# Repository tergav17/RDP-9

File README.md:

# RDP-9

## Project Description

This project aims to build an ISA-compatible clone of the DEC PDP-9 system using primarily technology from the late 1970s - early 1980s period. I did this to ensure my design followed the same constraints that later genuine minicomputer systems were built with, while being able to significantly reduce the size and complexity compared to an actual PDP-9. The specifics are as follows

- Use only 74-series logic and other similar TTL logic level parts that would be available around the later 1970s timeframe. The exception to this is RAM, which I plan to use more “modern” SRAM chips instead of torturing myself with dynamic RAM.
- No FPGAs, PALs, GALs, microcontrollers, etc in the main processor path. The only exception to this is using standard 27C style ROM chips to hold the microcode.
- Usage of a period correct microcontroller or microprocessor for the disk / drum subsystem. Using another simpler processor to control complex devices like disks was done frequently on other minicomputer designs, so I’ll be doing it here too.

My end goal is to build a system that is capable of running most of the interesting software of the period. This includes DECsys, ADSS, DOS-15, and UNIX V0. To do this, the system will need:

- Full compatibility with the PDP-9 instruction set. This includes EAE instructions and extended memory
- The ability to hook up to a real or emulated paper tape punch / reader.
- The ability to hook up to a real or emulated ASR-33 teletype or similar serial terminal
- 8" floppy drive interface in place of DECtape. Software will require patching but it's better than trying to emulate DECtape
- IDE hard drive support using RB09/RF09 interface 

## Theory of Operation

Due to the complexity involved with the architecture of the DEC PDP-9, the system is split into two subsystems:

The first subsystem is the processor itself. It has a full 18-bit datapath with 15-bit address bus, and is implemented entirely using TTL logic.

The second subsystem is the I/O bus. This is directly controlled by the processor itself and is capable of servicing the following operations:

- Device interrupts
- IOT transactions
- Add-to-memory operations
- Data channel transfers
- DMA transfers
- READ-IN operation

### Device Interrupts

Device interrupts simply tell the processor to begin an interrupt operation. When an interrupt is accepted, the I/O bus will be notified of the action
and is responsible for turning off the "Program Interrupt" flag. If this does not happen, interrupts will continuously loop. 

#### Steps:

1. Interrupt is accepted. MA is completely zeroed and the "INTERRUPT_DETECT" pulse is asserted for this clock cycle.

2. PC is stored in MB, OB

3. The logical OR of MB and OB is place in CORE at MA. The crossbar will add the LINK and MEMM flags

4. MA + 1 is placed in the PC. Extend is enabled to ensure that bank 0 is selected. The next fetch will ignore device requests

### IOT Transactions

IOT transactions allow data to be transferred to or from the accumulator. IOTs also allow for skips to be requested. Every IOT is treated by the CPU
as a Read-Modify-Write operation. By using the "EXTRN" signal, devices can notify the processor to read from the I/O bus instead of the writeback register.
When the I/O bus is being sampled, the "IOT_SKIP" signal can be asserted to tell the processor to perform an addition increment of the program counter.

A wait signal is sampled at the beginning of the IOT as well. This can be used to add cycles to the writeback phase of the IOT if the device needs it.

#### Steps:

1. IOT transaction begins. Device address is placed on the I/O address bus. AC (or 0 if the flag is set) is written to the WRTBK register.

2. Signal "IOT_PULSE" is asserted.

3. Signal "IOT_PULSE" remains asserted. External input is sampled into MB. Signal "EXTRN" must be asserted to take value from device bus.

4. IF "IOT_WAIT" is asserted, goto step 3 in place. No IOT signals are asserted. Interally, the CPU is performing the logical OR and writeback of potential provided data.

5. No IOT signals are asserted. Internally, the CPU will perform the skip here if it has been requested. The next fetch cycle will ignore interrupts and device requests.

### Device Requests

The final three transaction types (Add-to-memory, data-channels, and DMA transfers all share the "device request" pathway.

#### Steps:

1. Signal "REQ_ADDR_PHASE" and "DEV_REQ_GRANT" asserted and held. External value written to MA.

2. If DMA is selected, core is read at MA and written to WRTBK with next as step 8. Otherwise core is read at MA and written to MB, OB. "REQ_ADDR_PHASE" held

3. Value in MB, OB incremented and written back to core at MA and OB. "REQ_ADDR_PHASE" held

4. Value in MA incremented. If add to memory selected, Jump to fetch without device request logic. "INCREMENT_ZERO_PUSLE" will be generated if needed. "REQ_ADDR_PHASE" held

5. Core is read at MA and written to MB, OB.

6. Value in MB, OB incremented and written back to core at MA and MA

7. Core is read at MA and written to WRTBK

8. External value written to core at MA. "DEV_REQ_GRANT" reset. Jump to fetch without device request logic

### READ-IN Operation

The read-in is used to transfer a set series of words into memory from one of the I/O devices. Only one I/O device can be be allowed to respond to READ-IN
at any one time. When a READ-IN transaction is active, the CPU will stall until the designated device signals that it is ready. The device will either signal
the CPU to commence another READ-IN cycle, or to terminate the READ-IN after any given transfer.

#### Steps:

1. SWR is moved into PC

2. "READ_IN_PULSE" is asserted, step will loop till either "IOT_WAIT" or "IOT_SKIP" are asserted.

3. "READ_IN_PULSE" remains asserted. EXTRN is moved into core at PC. Continue having the constant value asserted.

4. "READ_IN_PULSE" reset. If "IOT_SKIP" is asserted, jump to CONT logic. Otherwise move PC + 1 into PC

5. Null phase, "READ_IN_PULSE" remains reset.

6. Null phase, "READ_IN_PULSE" remains reset. Jump to step 2 on completion

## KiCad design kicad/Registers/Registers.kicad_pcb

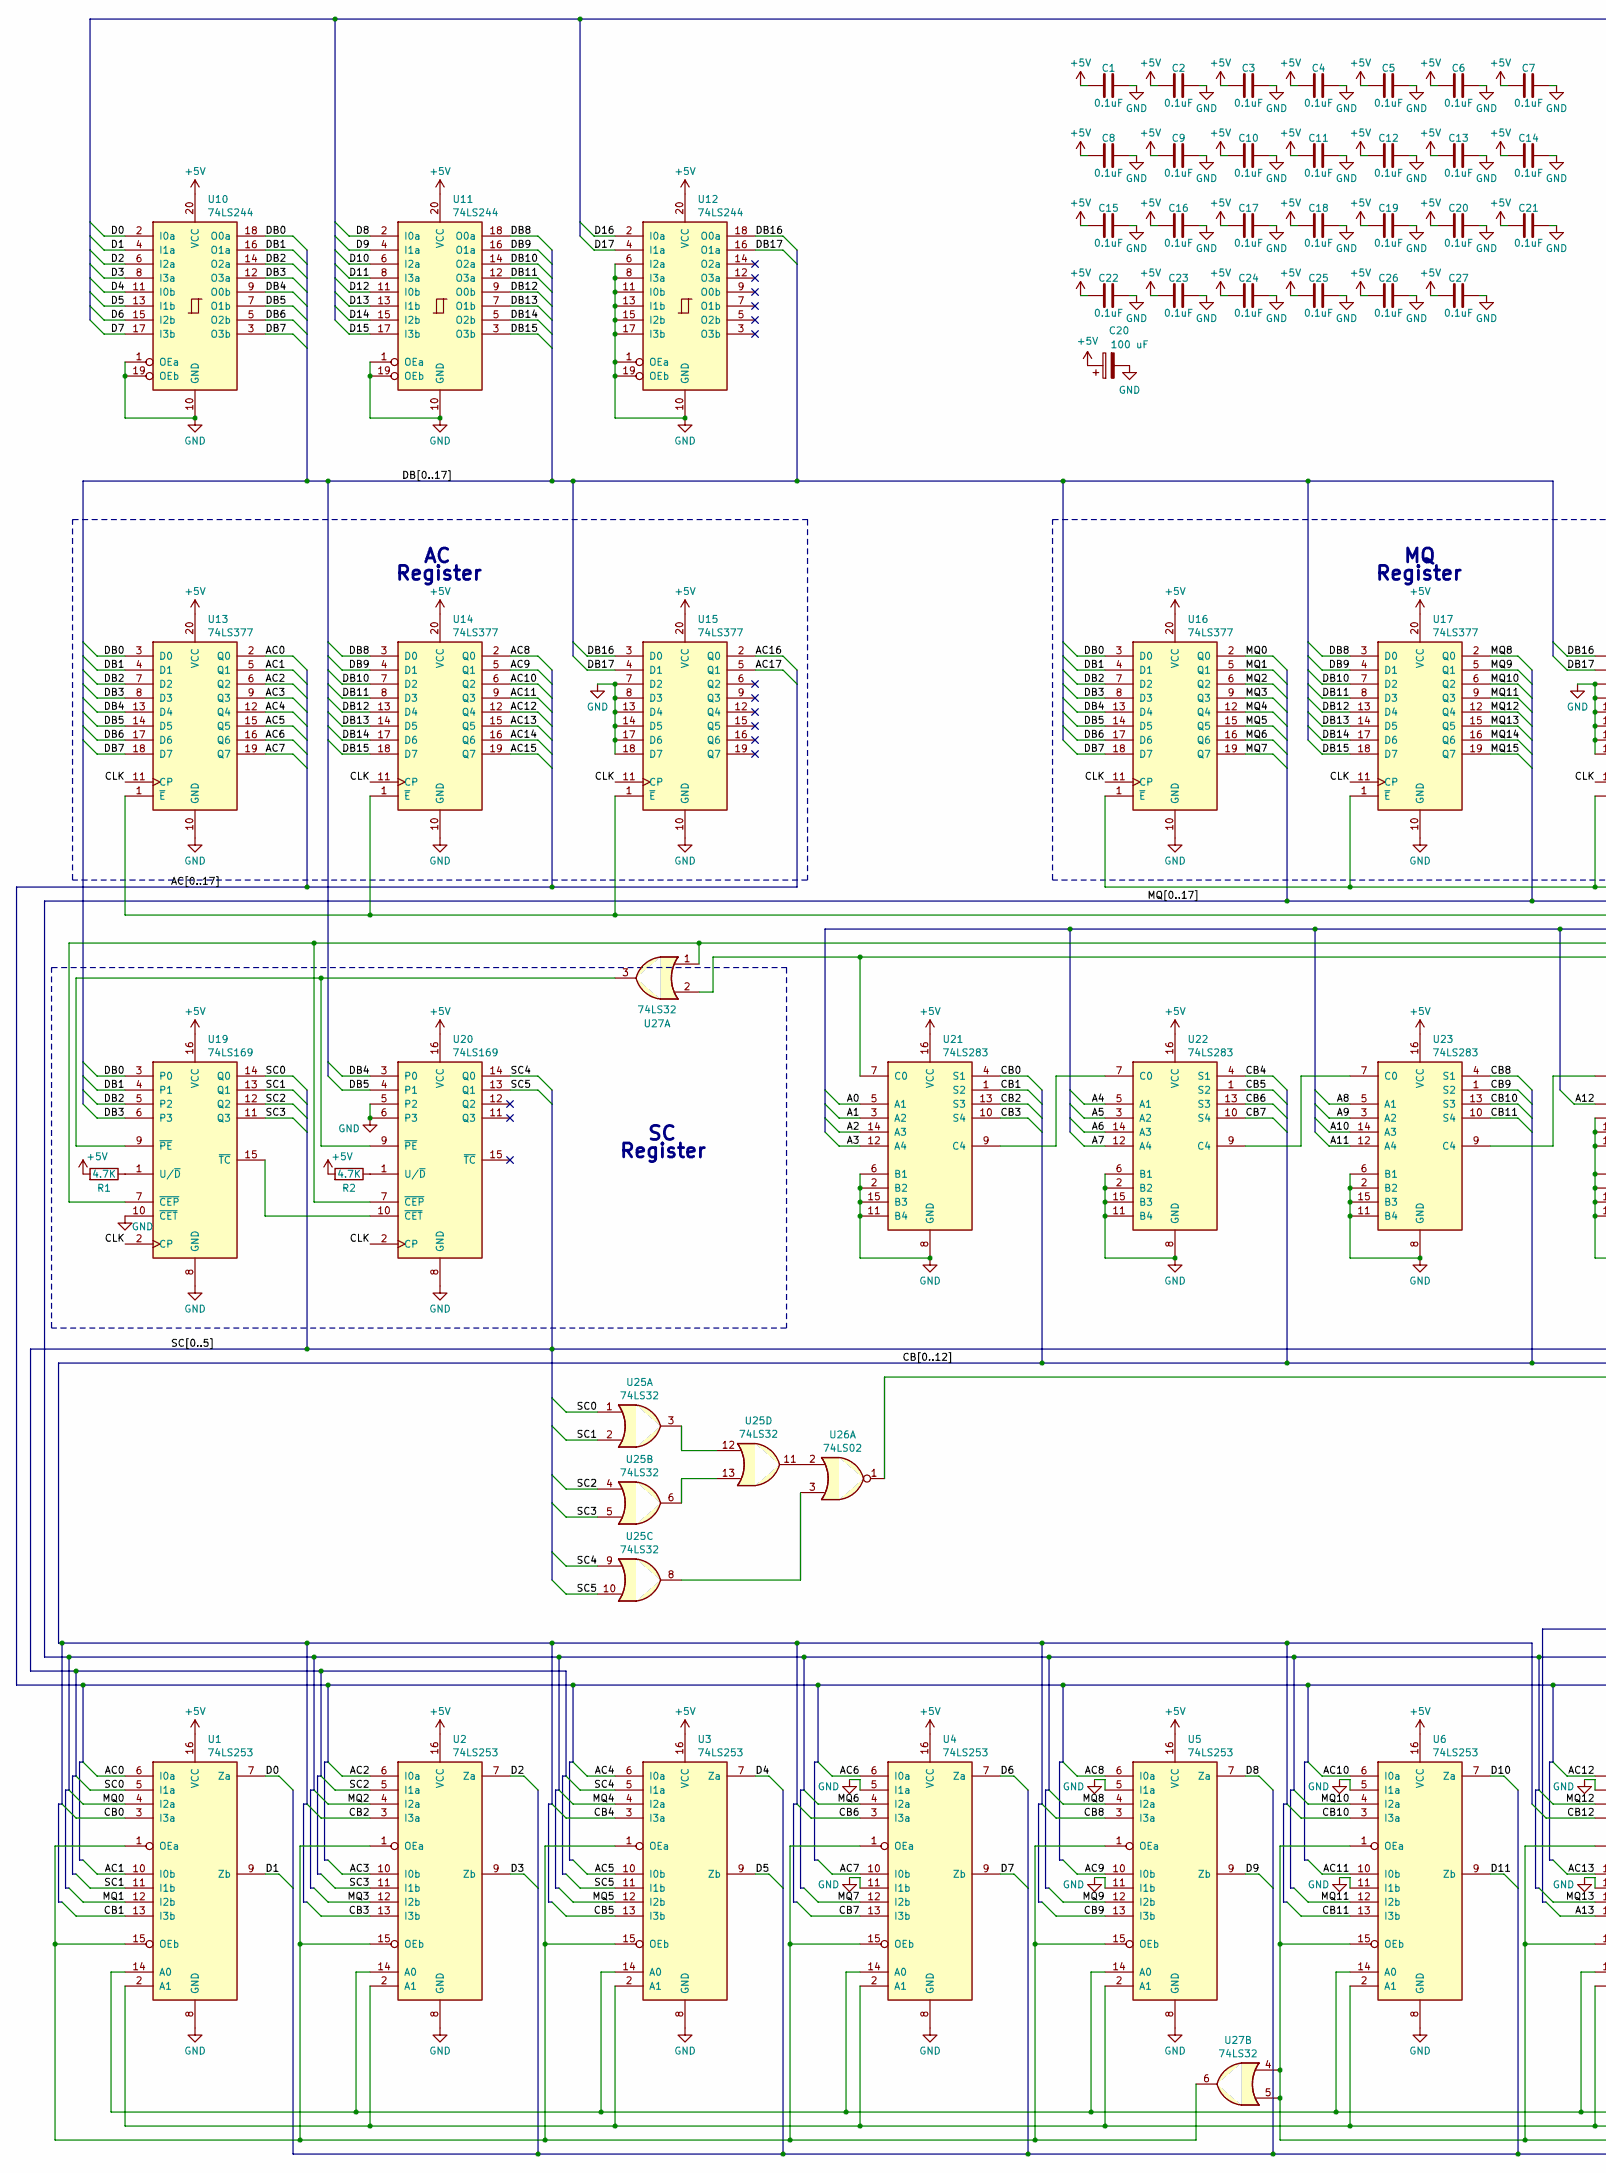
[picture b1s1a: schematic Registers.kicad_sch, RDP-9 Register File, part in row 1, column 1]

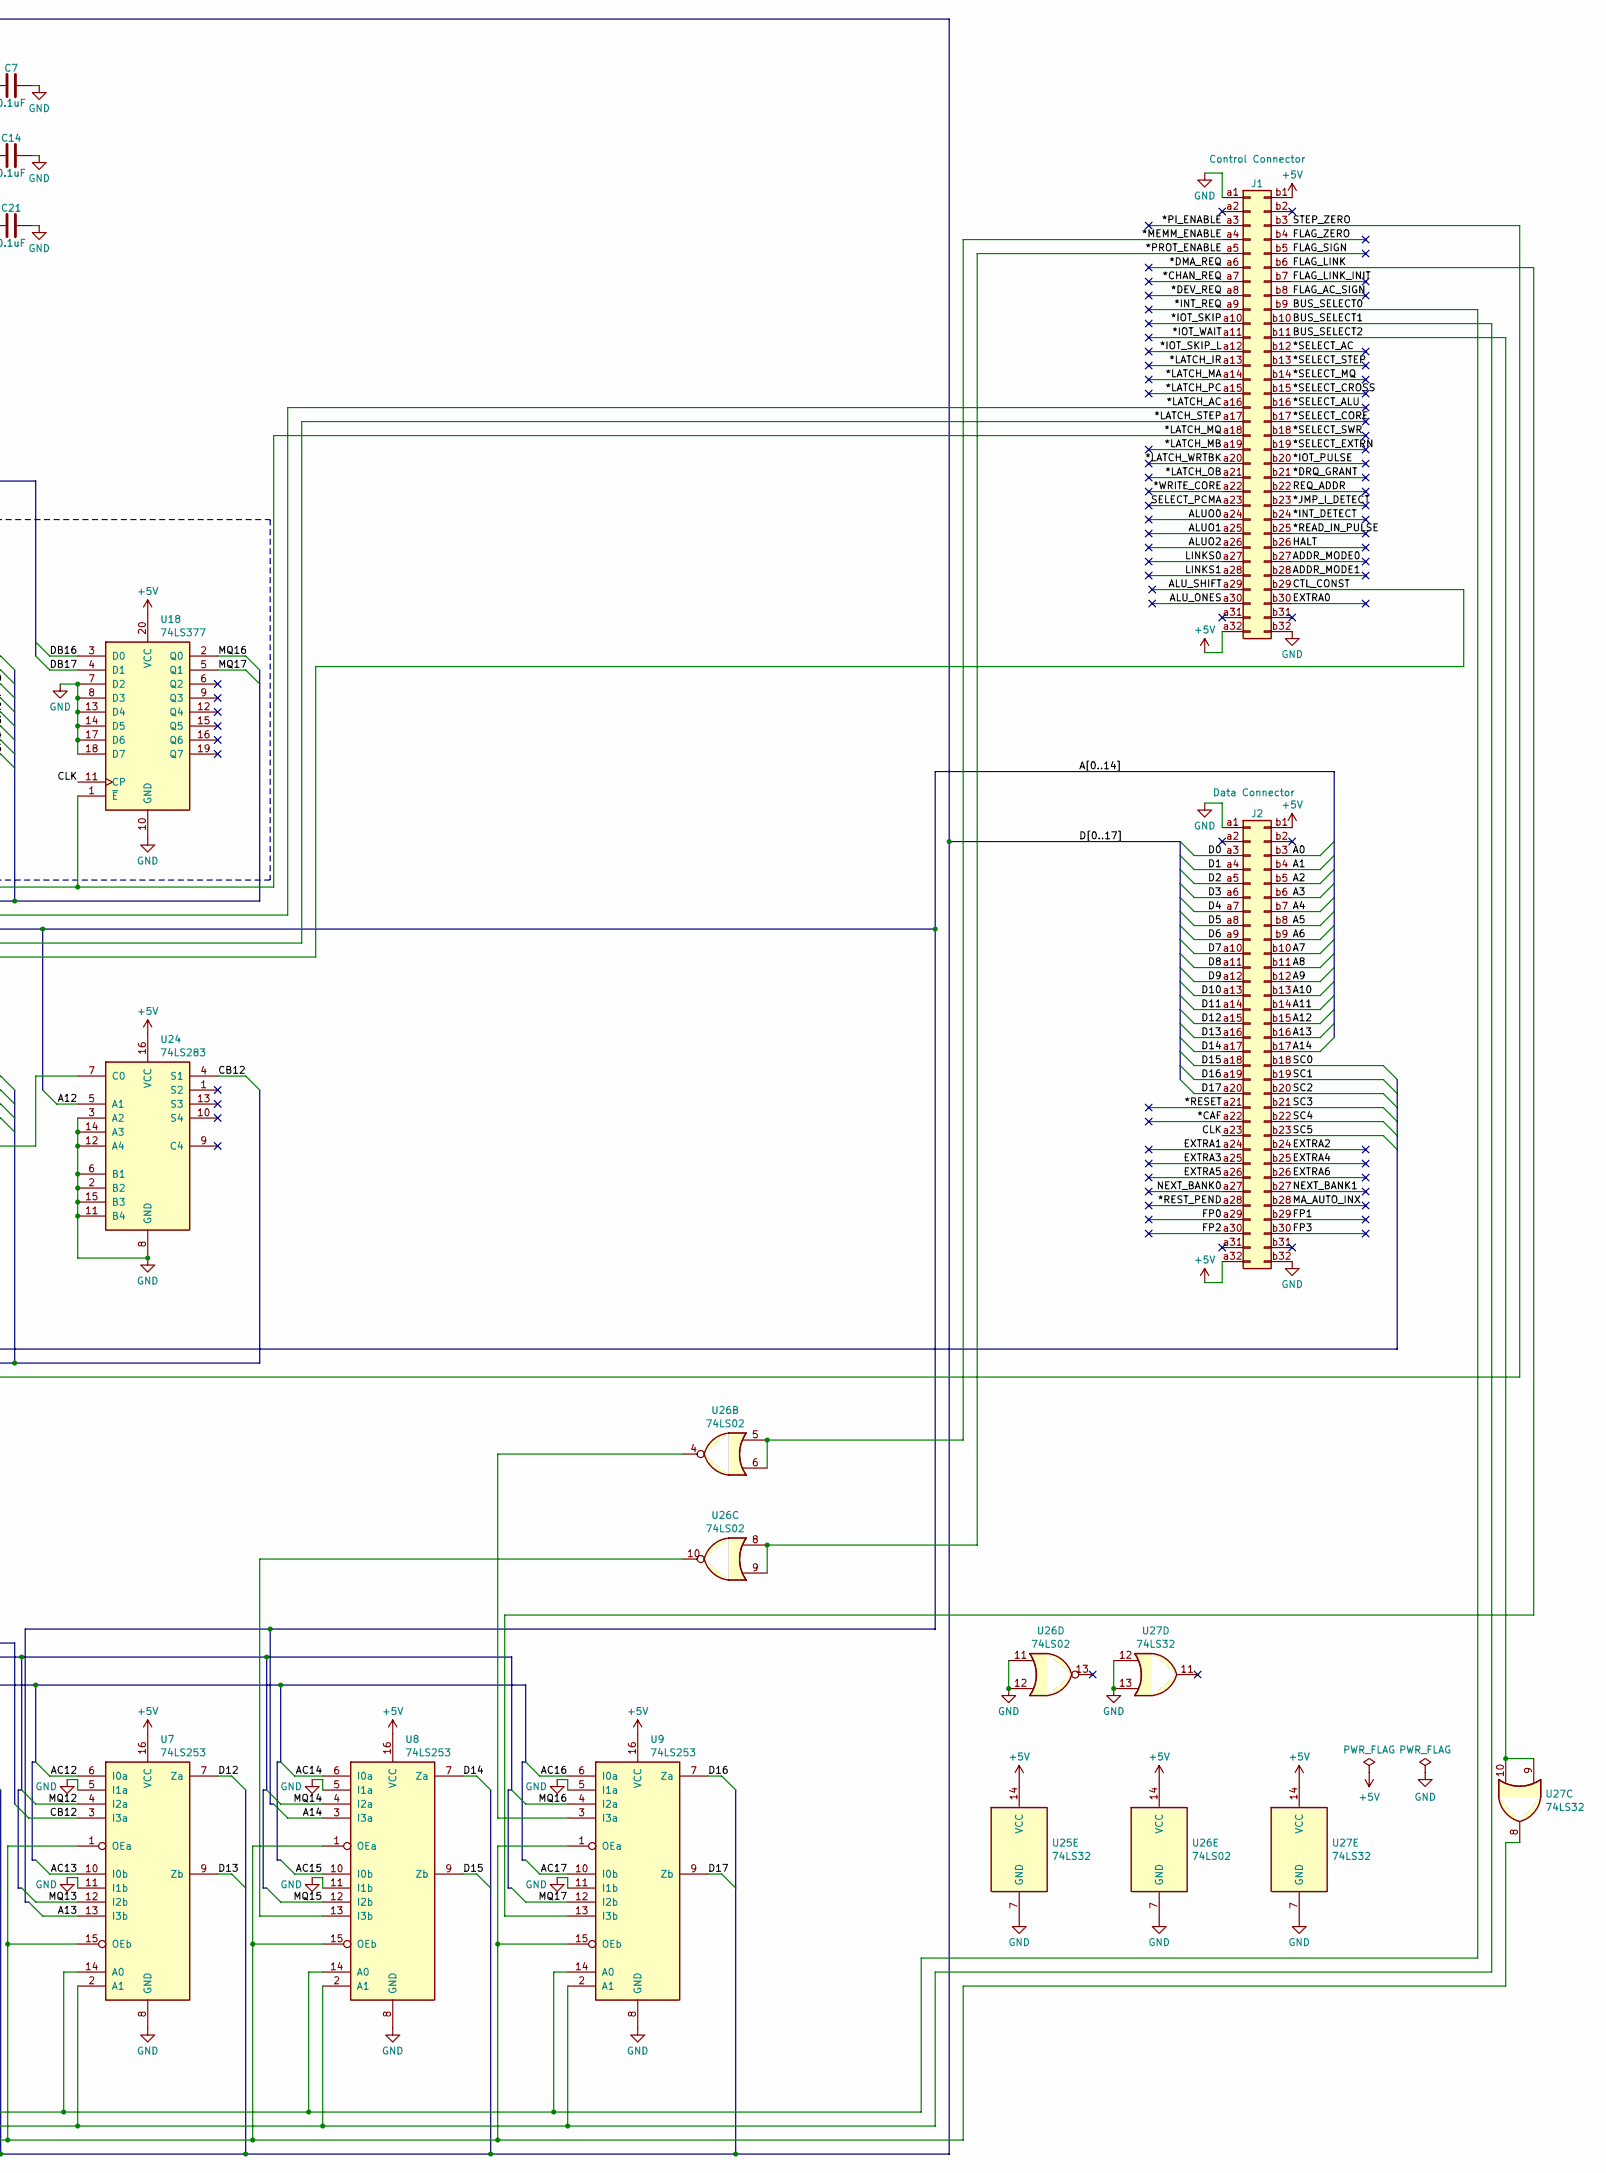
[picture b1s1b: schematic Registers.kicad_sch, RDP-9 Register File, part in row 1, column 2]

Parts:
C1, C2, C3, C4, C5, C6, C7, C8, C9, C10, C11, C12, C13, C14, C15, C16, C17, C18, C19, C21, C22, C23, C24, C25, C26, C27: 0.1uF; C_Disc_D5.0mm_W2.5mm_P5.00mm
C20: 100 uF; CP_Radial_D6.3mm_P2.50mm
J1: Control Connector; DIN41612_B_2x32_Male_Horizontal_THT
J2: Data Connector; DIN41612_B_2x32_Male_Horizontal_THT
R1, R2: 4.7K; R_Axial_DIN0207_L6.3mm_D2.5mm_P7.62mm_Horizontal
U1, U2, U3, U4, U5, U6, U7, U8, U9: 74LS253; DIP-16_W7.62mm
U10, U11, U12: 74LS244; DIP-20_W7.62mm
U13, U14, U15, U16, U17, U18: 74LS377; DIP-20_W7.62mm
U19, U20: 74LS169; DIP-16_W7.62mm
U21, U22, U23, U24: 74LS283; DIP-16_W7.62mm
U25, U27: 74LS32; DIP-14_W7.62mm
U26: 74LS02; DIP-14_W7.62mm

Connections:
+5V: C1.1, C2.1, C3.1, C4.1, C5.1, C6.1, C7.1, C8.1, C9.1, C10.1, C11.1, C12.1, C13.1, C14.1, C15.1, C16.1, C17.1, C18.1, C19.1, C20.1, C21.1, C22.1, C23.1, C24.1, C25.1, C26.1, C27.1, J1.a32, J1.b1, J2.a32, J2.b1, R1.2, R2.2, U1.16 (VCC), U2.16 (VCC), U3.16 (VCC), U4.16 (VCC), U5.16 (VCC), U6.16 (VCC), U7.16 (VCC), U8.16 (VCC), U9.16 (VCC), U10.20 (VCC), U11.20 (VCC), U12.20 (VCC), U13.20 (VCC), U14.20 (VCC), U15.20 (VCC), U16.20 (VCC), U17.20 (VCC), U18.20 (VCC), U19.16 (VCC), U20.16 (VCC), U21.16 (VCC), U22.16 (VCC), U23.16 (VCC), U24.16 (VCC), U25.14 (VCC), U26.14 (VCC), U27.14 (VCC); also elsewhere on the board
/*CAF: J2.a22
/*CHAN_REQ: J1.a7
/*DEV_REQ: J1.a8
/*DMA_REQ: J1.a6
/*DRQ_GRANT: J1.b21
/*INT_DETECT: J1.b24
/*INT_REQ: J1.a9
/*IOT_PULSE: J1.b20
/*IOT_SKIP: J1.a10
/*IOT_SKIP_L: J1.a12
/*IOT_WAIT: J1.a11
/*JMP_I_DETECT: J1.b23
/*LATCH_AC: J1.a16, U13.1 (~E), U14.1 (~E), U15.1 (~E)
/*LATCH_IR: J1.a13
/*LATCH_MA: J1.a14
/*LATCH_MB: J1.a19
/*LATCH_MQ: J1.a18, U16.1 (~E), U17.1 (~E), U18.1 (~E)
/*LATCH_OB: J1.a21
/*LATCH_PC: J1.a15
/*LATCH_STEP: J1.a17, U19.7 (~CEP), U20.7 (~CEP), U27.1
/*LATCH_WRTBK: J1.a20
/*MEMM_ENABLE: J1.a4, U26.5, U26.6
/*PI_ENABLE: J1.a3
/*PROT_ENABLE: J1.a5, U26.8, U26.9
/*READ_IN_PULSE: J1.b25
/*RESET: J2.a21
/*REST_PEND: J2.a28
/*SELECT_AC: J1.b12
/*SELECT_ALU: J1.b16
/*SELECT_CORE: J1.b17
/*SELECT_CROSS: J1.b15
/*SELECT_EXTRN: J1.b19
/*SELECT_MQ: J1.b14
/*SELECT_STEP: J1.b13
/*SELECT_SWR: J1.b18
/*WRITE_CORE: J1.a22
/A0: J2.b3, U21.5 (A1)
/A1: J2.b4, U21.3 (A2)
/A2: J2.b5, U21.14 (A3)
/A3: J2.b6, U21.12 (A4)
/A4: J2.b7, U22.5 (A1)
/A5: J2.b8, U22.3 (A2)
/A6: J2.b9, U22.14 (A3)
/A7: J2.b10, U22.12 (A4)
/A8: J2.b11, U23.5 (A1)
/A9: J2.b12, U23.3 (A2)
/A10: J2.b13, U23.14 (A3)
/A11: J2.b14, U23.12 (A4)
/A12: J2.b15, U24.5 (A1)
/A13: J2.b16, U7.13 (I3b)
/A14: J2.b17, U8.3 (I3a)
/AC0: U1.6 (I0a), U13.2 (Q0)
/AC1: U1.10 (I0b), U13.5 (Q1)
/AC2: U2.6 (I0a), U13.6 (Q2)
/AC3: U2.10 (I0b), U13.9 (Q3)
/AC4: U3.6 (I0a), U13.12 (Q4)
/AC5: U3.10 (I0b), U13.15 (Q5)
/AC6: U4.6 (I0a), U13.16 (Q6)
/AC7: U4.10 (I0b), U13.19 (Q7)
/AC8: U5.6 (I0a), U14.2 (Q0)
/AC9: U5.10 (I0b), U14.5 (Q1)
/AC10: U6.6 (I0a), U14.6 (Q2)
/AC11: U6.10 (I0b), U14.9 (Q3)
/AC12: U7.6 (I0a), U14.12 (Q4)
/AC13: U7.10 (I0b), U14.15 (Q5)
/AC14: U8.6 (I0a), U14.16 (Q6)
/AC15: U8.10 (I0b), U14.19 (Q7)
/AC16: U9.6 (I0a), U15.2 (Q0)
/AC17: U9.10 (I0b), U15.5 (Q1)
/ADDR_MODE0: J1.b27
/ADDR_MODE1: J1.b28
/ALUO0: J1.a24
/ALUO1: J1.a25
/ALUO2: J1.a26
/ALU_ONES: J1.a30
/ALU_SHIFT: J1.a29
/BUS_SELECT0: J1.b9, U1.14 (A0), U2.14 (A0), U3.14 (A0), U4.14 (A0), U5.14 (A0), U6.14 (A0), U7.14 (A0), U8.14 (A0), U9.14 (A0)
/BUS_SELECT1: J1.b10, U1.2 (A1), U2.2 (A1), U3.2 (A1), U4.2 (A1), U5.2 (A1), U6.2 (A1), U7.2 (A1), U8.2 (A1), U9.2 (A1)
/BUS_SELECT2: J1.b11, U27.9, U27.10
/CB0: U1.3 (I3a), U21.4 (S1)
/CB1: U1.13 (I3b), U21.1 (S2)
/CB2: U2.3 (I3a), U21.13 (S3)
/CB3: U2.13 (I3b), U21.10 (S4)
/CB4: U3.3 (I3a), U22.4 (S1)
/CB5: U3.13 (I3b), U22.1 (S2)
/CB6: U4.3 (I3a), U22.13 (S3)
/CB7: U4.13 (I3b), U22.10 (S4)
/CB8: U5.3 (I3a), U23.4 (S1)
/CB9: U5.13 (I3b), U23.1 (S2)
/CB10: U6.3 (I3a), U23.13 (S3)
/CB11: U6.13 (I3b), U23.10 (S4)
/CB12: U7.3 (I3a), U24.4 (S1)
/CLK: J2.a23, U13.11 (CP), U14.11 (CP), U15.11 (CP), U16.11 (CP), U17.11 (CP), U18.11 (CP), U19.2 (CP), U20.2 (CP)
/CTL_CONST: J1.b29, U21.7 (C0), U27.2
/D0: J2.a3, U1.7 (Za), U10.2 (I0a)
/D1: J2.a4, U1.9 (Zb), U10.4 (I1a)
/D2: J2.a5, U2.7 (Za), U10.6 (I2a)
/D3: J2.a6, U2.9 (Zb), U10.8 (I3a)
/D4: J2.a7, U3.7 (Za), U10.11 (I0b)
/D5: J2.a8, U3.9 (Zb), U10.13 (I1b)
/D6: J2.a9, U4.7 (Za), U10.15 (I2b)
/D7: J2.a10, U4.9 (Zb), U10.17 (I3b)
/D8: J2.a11, U5.7 (Za), U11.2 (I0a)
/D9: J2.a12, U5.9 (Zb), U11.4 (I1a)
/D10: J2.a13, U6.7 (Za), U11.6 (I2a)
/D11: J2.a14, U6.9 (Zb), U11.8 (I3a)
/D12: J2.a15, U7.7 (Za), U11.11 (I0b)
/D13: J2.a16, U7.9 (Zb), U11.13 (I1b)
/D14: J2.a17, U8.7 (Za), U11.15 (I2b)
/D15: J2.a18, U8.9 (Zb), U11.17 (I3b)
/D16: J2.a19, U9.7 (Za), U12.2 (I0a)
/D17: J2.a20, U9.9 (Zb), U12.4 (I1a)
/DB0: U10.18 (O0a), U13.3 (D0), U16.3 (D0), U19.3 (P0)
/DB1: U10.16 (O1a), U13.4 (D1), U16.4 (D1), U19.4 (P1)
/DB2: U10.14 (O2a), U13.7 (D2), U16.7 (D2), U19.5 (P2)
/DB3: U10.12 (O3a), U13.8 (D3), U16.8 (D3), U19.6 (P3)
/DB4: U10.9 (O0b), U13.13 (D4), U16.13 (D4), U20.3 (P0)
/DB5: U10.7 (O1b), U13.14 (D5), U16.14 (D5), U20.4 (P1)
/DB6: U10.5 (O2b), U13.17 (D6), U16.17 (D6)
/DB7: U10.3 (O3b), U13.18 (D7), U16.18 (D7)
/DB8: U11.18 (O0a), U14.3 (D0), U17.3 (D0)
/DB9: U11.16 (O1a), U14.4 (D1), U17.4 (D1)
/DB10: U11.14 (O2a), U14.7 (D2), U17.7 (D2)
/DB11: U11.12 (O3a), U14.8 (D3), U17.8 (D3)
/DB12: U11.9 (O0b), U14.13 (D4), U17.13 (D4)
/DB13: U11.7 (O1b), U14.14 (D5), U17.14 (D5)
/DB14: U11.5 (O2b), U14.17 (D6), U17.17 (D6)
/DB15: U11.3 (O3b), U14.18 (D7), U17.18 (D7)
/DB16: U12.18 (O0a), U15.3 (D0), U18.3 (D0)
/DB17: U12.16 (O1a), U15.4 (D1), U18.4 (D1)
/EXTRA0: J1.b30
/EXTRA1: J2.a24
/EXTRA2: J2.b24
/EXTRA3: J2.a25
/EXTRA4: J2.b25
/EXTRA5: J2.a26
/EXTRA6: J2.b26
/FLAG_AC_SIGN: J1.b8
/FLAG_LINK: J1.b6, U9.13 (I3b)
/FLAG_LINK_INIT: J1.b7
/FLAG_SIGN: J1.b5
/FLAG_ZERO: J1.b4
/FP0: J2.a29
/FP1: J2.b29
/FP2: J2.a30
/FP3: J2.b30
/HALT: J1.b26
/LINKS0: J1.a27
/LINKS1: J1.a28
/MA_AUTO_INX: J2.b28
/MQ0: U1.4 (I2a), U16.2 (Q0)
/MQ1: U1.12 (I2b), U16.5 (Q1)
/MQ2: U2.4 (I2a), U16.6 (Q2)
/MQ3: U2.12 (I2b), U16.9 (Q3)
/MQ4: U3.4 (I2a), U16.12 (Q4)
/MQ5: U3.12 (I2b), U16.15 (Q5)
/MQ6: U4.4 (I2a), U16.16 (Q6)
/MQ7: U4.12 (I2b), U16.19 (Q7)
/MQ8: U5.4 (I2a), U17.2 (Q0)
/MQ9: U5.12 (I2b), U17.5 (Q1)
/MQ10: U6.4 (I2a), U17.6 (Q2)
/MQ11: U6.12 (I2b), U17.9 (Q3)
/MQ12: U7.4 (I2a), U17.12 (Q4)
/MQ13: U7.12 (I2b), U17.15 (Q5)
/MQ14: U8.4 (I2a), U17.16 (Q6)
/MQ15: U8.12 (I2b), U17.19 (Q7)
/MQ16: U9.4 (I2a), U18.2 (Q0)
/MQ17: U9.12 (I2b), U18.5 (Q1)
/NEXT_BANK0: J2.a27
/NEXT_BANK1: J2.b27
/REQ_ADDR: J1.b22
/SC0: J2.b18, U1.5 (I1a), U19.14 (Q0), U25.1
/SC1: J2.b19, U1.11 (I1b), U19.13 (Q1), U25.2
/SC2: J2.b20, U2.5 (I1a), U19.12 (Q2), U25.4
/SC3: J2.b21, U2.11 (I1b), U19.11 (Q3), U25.5
/SC4: J2.b22, U3.5 (I1a), U20.14 (Q0), U25.9
/SC5: J2.b23, U3.11 (I1b), U20.13 (Q1), U25.10
/SELECT_PCMA: J1.a23
/STEP_ZERO: J1.b3, U26.1
GND: C1.2, C2.2, C3.2, C4.2, C5.2, C6.2, C7.2, C8.2, C9.2, C10.2, C11.2, C12.2, C13.2, C14.2, C15.2, C16.2, C17.2, C18.2, C19.2, C20.2, C21.2, C22.2, C23.2, C24.2, C25.2, C26.2, C27.2, J1.a1, J1.b32, J2.a1, J2.b32, U1.8 (GND), U2.8 (GND), U3.8 (GND), U4.5 (I1a), U4.8 (GND), U4.11 (I1b), U5.5 (I1a), U5.8 (GND), U5.11 (I1b), U6.5 (I1a), U6.8 (GND), U6.11 (I1b), U7.5 (I1a), U7.8 (GND), U7.11 (I1b), U8.5 (I1a), U8.8 (GND), U8.11 (I1b), U9.5 (I1a), U9.8 (GND), U9.11 (I1b), U10.1 (OEa), U10.10 (GND), U10.19 (OEb), U11.1 (OEa), U11.10 (GND), U11.19 (OEb), U12.1 (OEa), U12.6 (I2a), U12.8 (I3a), U12.10 (GND), U12.11 (I0b), U12.13 (I1b), U12.15 (I2b), U12.17 (I3b), U12.19 (OEb), U13.10 (GND), U14.10 (GND), U15.7 (D2), U15.8 (D3), U15.10 (GND), U15.13 (D4), U15.14 (D5), U15.17 (D6), U15.18 (D7), U16.10 (GND), U17.10 (GND), U18.7 (D2), U18.8 (D3), U18.10 (GND), U18.13 (D4), U18.14 (D5), U18.17 (D6), U18.18 (D7), U19.8 (GND), U19.10 (~CET), U20.5 (P2), U20.6 (P3), U20.8 (GND), U21.2 (B2), U21.6 (B1), U21.8 (GND), U21.11 (B4), U21.15 (B3), U22.2 (B2), U22.6 (B1), U22.8 (GND), U22.11 (B4), U22.15 (B3), U23.2 (B2), U23.6 (B1), U23.8 (GND), U23.11 (B4), U23.15 (B3), U24.2 (B2), U24.3 (A2), U24.6 (B1), U24.8 (GND), U24.11 (B4), U24.12 (A4), U24.14 (A3), U24.15 (B3), U25.7 (GND), U26.7 (GND), U26.11, U26.12, U27.7 (GND), U27.12, U27.13; also elsewhere on the board
unnamed: U1.1 (OEa), U1.15 (OEb), U2.1 (OEa), U2.15 (OEb), U3.1 (OEa), U3.15 (OEb), U4.1 (OEa), U4.15 (OEb), U5.1 (OEa), U5.15 (OEb), U27.6
unnamed: U6.1 (OEa), U6.15 (OEb), U7.1 (OEa), U7.15 (OEb), U8.1 (OEa), U8.15 (OEb), U9.1 (OEa), U9.15 (OEb), U27.4, U27.5, U27.8
unnamed: U8.13 (I3b), U26.10
unnamed: U9.3 (I3a), U26.4
unnamed: R1.1, U19.1 (U/~D)
unnamed: U19.9 (~PE), U20.9 (~PE), U27.3
unnamed: U19.15 (~TC), U20.10 (~CET)
unnamed: R2.1, U20.1 (U/~D)
unnamed: U21.9 (C4), U22.7 (C0)
unnamed: U22.9 (C4), U23.7 (C0)
unnamed: U23.9 (C4), U24.7 (C0)
unnamed: U25.8, U26.3
unnamed: U25.11, U26.2
unnamed: U25.3, U25.12
unnamed: U25.6, U25.13

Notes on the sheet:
Register

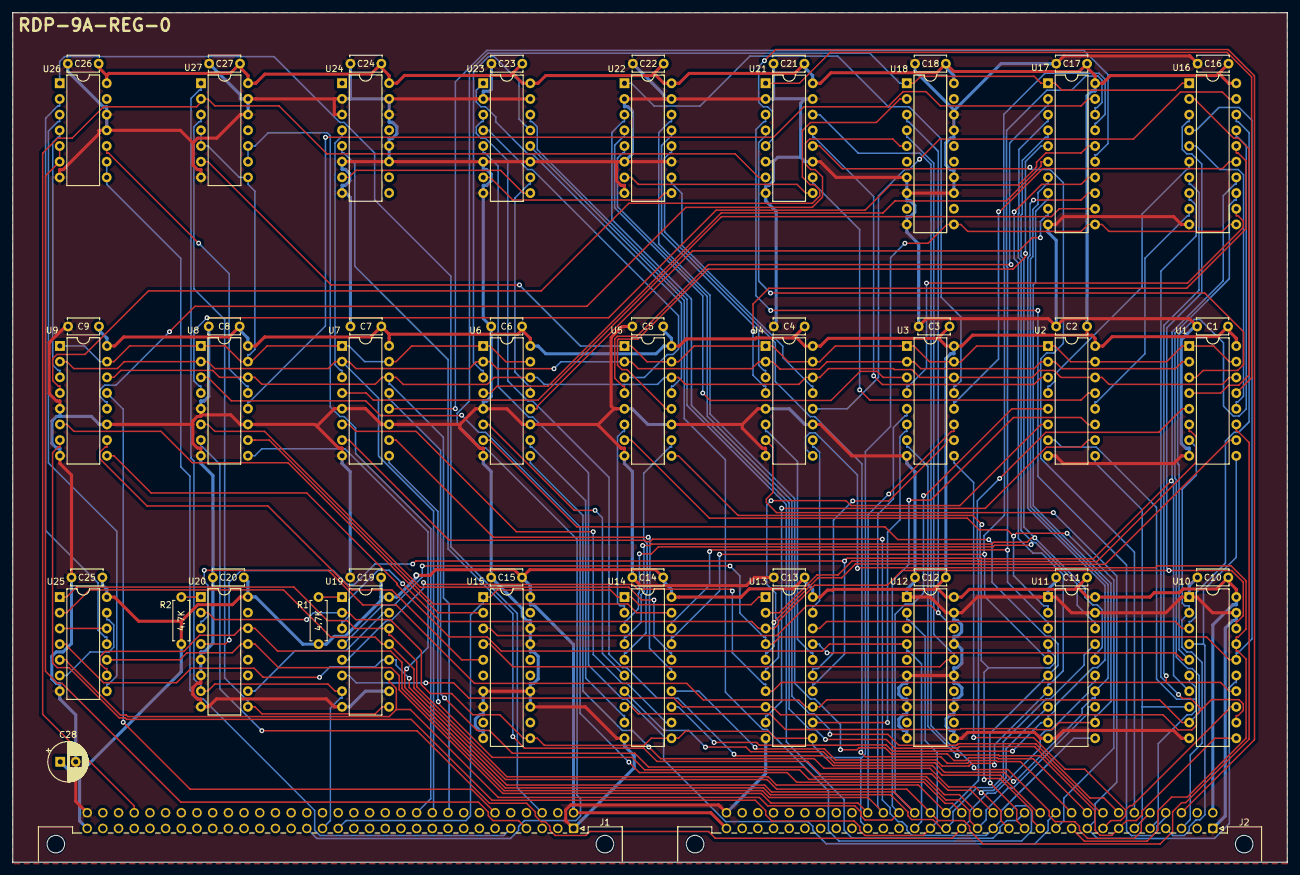
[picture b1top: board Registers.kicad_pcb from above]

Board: 2 copper layers, 206.4 x 137.5 mm, 59 parts (0 on the bottom side), 135 nets.

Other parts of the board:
C28: 100 uF; CP_Radial_D6.3mm_P2.50mm

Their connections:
+5V: C28.1; also elsewhere on the board
GND: C28.2; also elsewhere on the board
